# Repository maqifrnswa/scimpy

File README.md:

# Scimpy
Scimpy Speaker Design Tool
Open Source Sound Card Based Speaker Impedance Measurements, Speaker Design Tool, and Book on Loudspeaker Operation

## Requirements
Python 3, Qt4, PortAudio

### General Python Requirements:

scipy, pyaudio, matplotlib, pandas and either pyqt4 or pyside

### Debian/Ubuntu development environment:

```
sudo apt-get install python3-scipy python3-pyaudio python3-matplotlib python3-pyside python3-pandas
```

### Windows Python Environment 
& Scimpy Installation:

#### Full install (LARGE), comes with spyder IDE and many other python packages

install anaconda (https://www.continuum.io/downloads), open anaconda console and then in the anaconda console run "pip install pyaudio".

If you want more control over the sound card, you can use a version of pyaudio built with more APIs available. Download pyaudio from:
http://www.lfd.uci.edu/~gohlke/pythonlibs/ then open the anaconda console and install pyaudio
with "pip install PyAudio-0.2.9-cp35-none-win_amd64.whl"
replacing PyAudio-0.2.9-cp35-none-win_amd64.whl with the name of the file you downloaded.

#### Minimal install:

Install miniconda (32bit, even if you have 64 bit - makes things easier) from:
http://conda.pydata.org/miniconda.html

Open Windows PowerShell (Start Menu, search for "Windows PowerShell") and type the following commands:

```
conda update conda
conda install matplotlib scipy numpy
pip install pyaudio
cd LOCATION_WHERE_SCIMPY_WAS_DOWNLOADED
python run.py
```

have fun!

#### How to build Windows binaries

PyInstaller works. First install pyinstaller:

```
pip install pywin32 pyinstaller
conda install setuptools=19.2
```

(downgrading setuptools: https://github.com/pyinstaller/pyinstaller/issues/1781)

The run

```
pyinstaller -F --additional-hooks-dir=pyinstaller-hooks run.py
```

to get a single executable in dist/

### Book
LaTeX (e.g., MiKTeX)
http://miktex.org/

## License
Code: GPL3

Book/Documentation: CC-BY-SA 4.0

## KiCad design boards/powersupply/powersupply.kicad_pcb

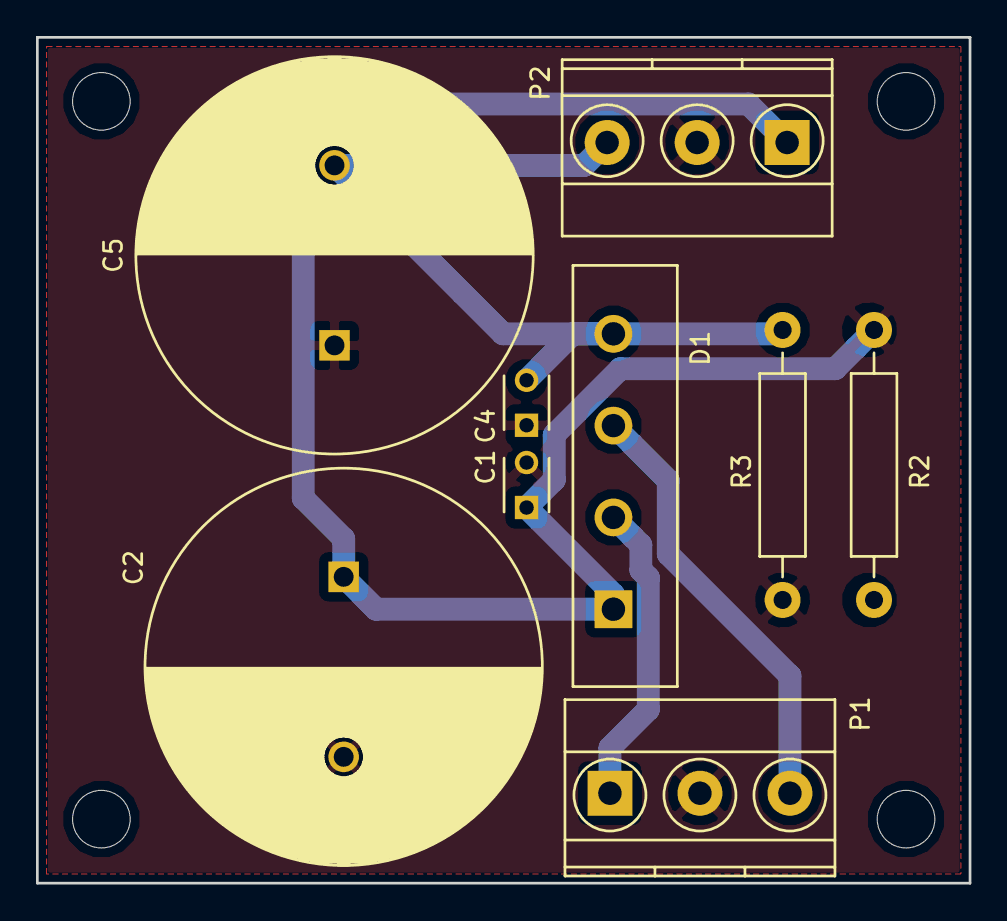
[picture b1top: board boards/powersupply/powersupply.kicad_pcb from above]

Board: 2 copper layers, 51.8 x 47.0 mm, 9 parts (0 on the bottom side), 5 nets.

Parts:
C1, C4: 100n; C_Disc_D3_P2.5
C2, C5: 6800u; C_Radial_D22_L41_P10
D1: Diode_Bridge; Diode_Bridge_18.5x5.5
P1, P2: CONN_01X03; TerminalBlock_Pheonix_MKDS1.5-3pol
R2, R3: 1K 1W; Resistor_Horizontal_RM15mm

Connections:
+15V: C1.1, C2.1, D1.3, P2.1, R2.1
-15V: C4.2, C5.2, D1.1, P2.3, R3.2
/+12VAC: D1.4, P1.3
/-12VAC: D1.2, P1.1
GND: C1.2, C2.2, C4.1, C5.1, P1.2, P2.2, R2.2, R3.1

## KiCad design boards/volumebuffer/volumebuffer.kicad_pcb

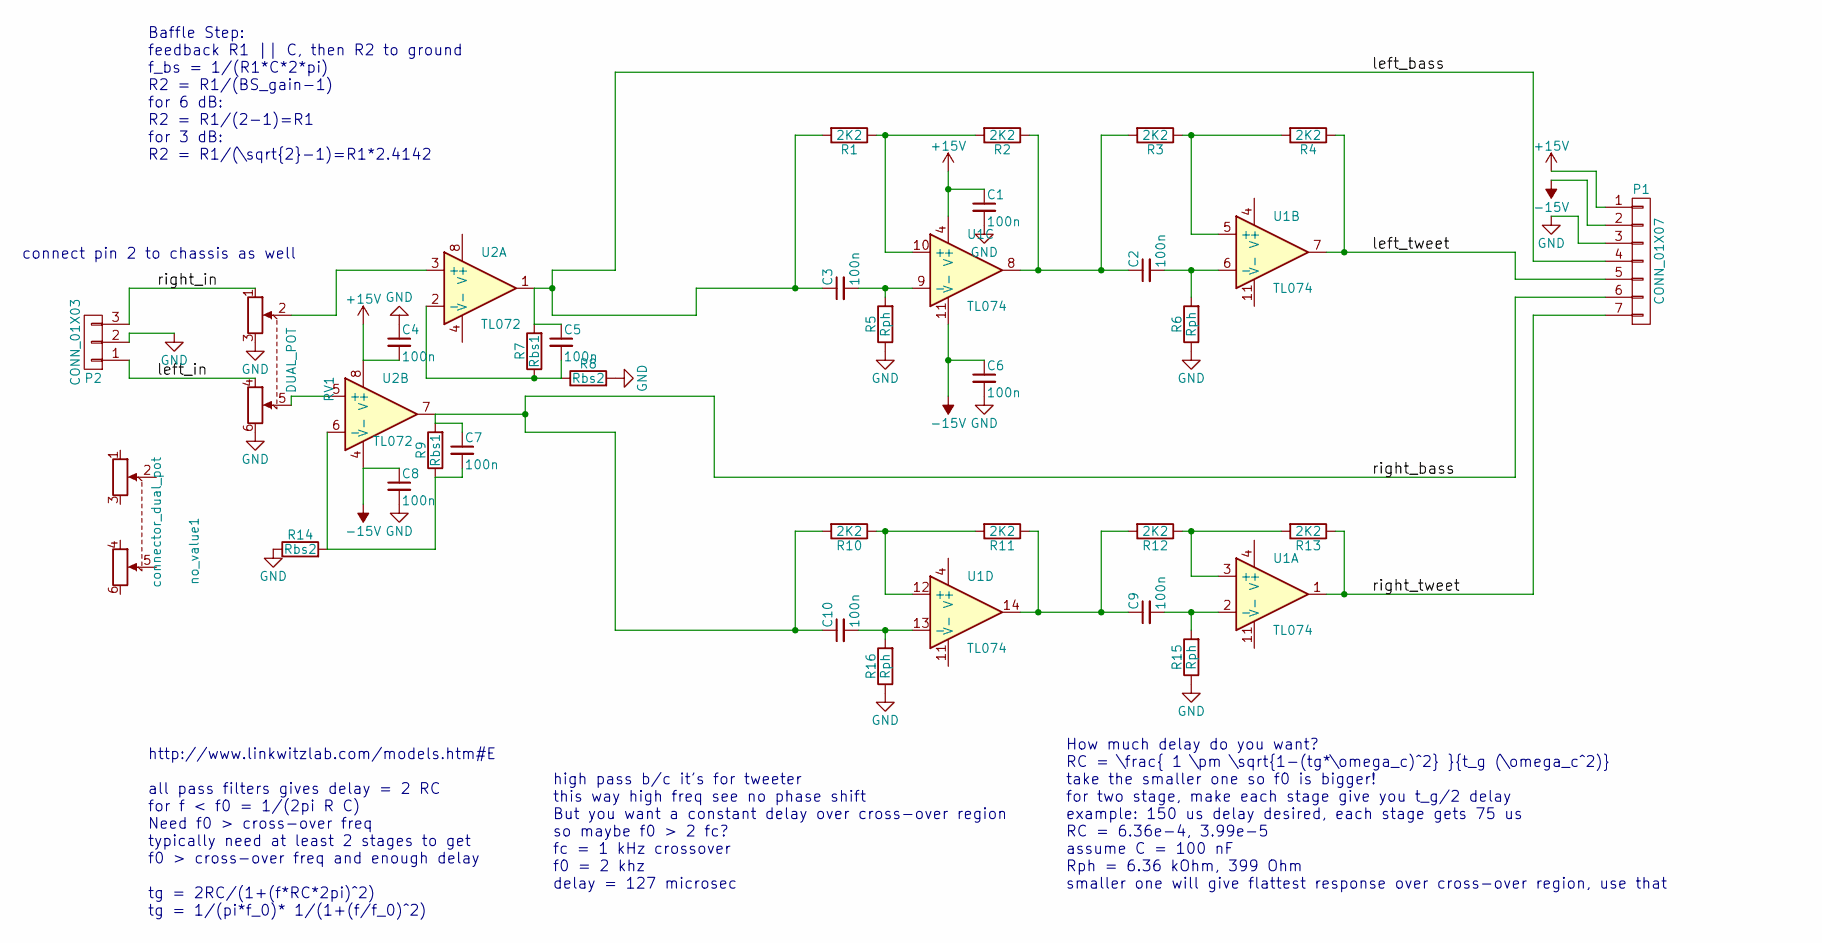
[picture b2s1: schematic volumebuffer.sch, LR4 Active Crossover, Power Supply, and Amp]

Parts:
C1, C4, C6, C8: 100n; C_Disc_D3_P2.5
C2, C3, C5, C7, C9, C10: 100n; C_Disc_D6_P5
P1: CONN_01X07; Socket_Strip_Angled_1x07
P2: CONN_01X03; TerminalBlock_Pheonix_MKDS1.5-3pol
R1, R2, R3, R4, R10, R11, R12, R13: 2K2; R_Axial_DIN0204_L3.6mm_D1.6mm_P5.08mm_Horizontal
R5, R6, R15, R16: Rph; R_Axial_DIN0204_L3.6mm_D1.6mm_P5.08mm_Horizontal
R7, R9: Rbs1; R_Axial_DIN0204_L3.6mm_D1.6mm_P5.08mm_Horizontal
R8, R14: Rbs2; R_Axial_DIN0204_L3.6mm_D1.6mm_P5.08mm_Horizontal
RV1: DUAL_POT; Molex_KK-6410-06_06x2.54mm_Straight
U1: TL074; DIP-14_W7.62mm
U2: TL072; DIP-8_W7.62mm
no_value1: connector_dual_pot

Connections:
+15V: C1.1, C4.2, P1.1, U1.4 (V+), U2.8 (V+)
-15V: C6.1, C8.1, P1.2, U1.11 (V-), U2.4 (V-)
/left_bass: C3.1, C5.1, P1.4, R1.2, R7.2, U2.1
/left_in: P2.1, RV1.4
/left_tweet: P1.5, R4.1, U1.7
/right_bass: C7.1, C10.1, P1.6, R9.2, R10.2, U2.7
/right_in: P2.3, RV1.1
/right_tweet: P1.7, R13.1, U1.1
GND: C1.2, C4.1, C6.2, C8.2, P1.3, P2.2, R5.1, R6.1, R8.2, R14.1, R15.1, R16.1, RV1.3, RV1.6
unnamed: C2.1, R2.1, R3.2, U1.8
unnamed: C2.2, R6.2, U1.6 (-)
unnamed: C3.2, R5.2, U1.9 (-)
unnamed: C5.2, R7.1, R8.1, U2.2 (-)
unnamed: C7.2, R9.1, R14.2, U2.6 (-)
unnamed: C9.1, R11.1, R12.2, U1.14
unnamed: C9.2, R15.2, U1.2 (-)
unnamed: C10.2, R16.2, U1.13 (-)
unnamed: R1.1, R2.2, U1.10 (+)
unnamed: R3.1, R4.2, U1.5 (+)
unnamed: R10.1, R11.2, U1.12 (+)
unnamed: R12.1, R13.2, U1.3 (+)
unnamed: RV1.2, U2.3 (+)
unnamed: RV1.5, U2.5 (+)

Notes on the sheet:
Baffle Step: feedback R1 || C, then R2 to ground f_bs = 1/(R1*C*2*pi) R2 = R1/(BS_gain-1) for 6 dB: R2 = R1/(2-1)=R1 for 3 dB: R2 = R1/(\sqrt{2}-1)=R1*2.4142
connect pin 2 to chassis as well
http://www.linkwitzlab.com/models.htm#E all pass filters gives delay = 2 RC for f < f0 = 1/(2pi R C) Need f0 > cross-over freq typically need at least 2 stages to get f0 > cross-over freq and enough delay tg = 2RC/(1+(f*RC*2pi)^2) tg = 1/(pi*f_0)* 1/(1+(f/f_0)^2)
high pass b/c it's for tweeter this way high freq see no phase shift But you want a constant delay over cross-over region so maybe f0 > 2 fc? fc = 1 kHz crossover f0 = 2 khz delay = 127 microsec
How much delay do you want? RC = \frac{ 1 \pm \sqrt{1-(tg*\omega_c)^2} }{t_g (\omega_c^2)} take the smaller one so f0 is bigger! for two stage, make each stage give you t_g/2 delay example: 150 us delay desired, each stage gets 75 us RC = 6.36e-4, 3.99e-5 assume C = 100 nF Rph = 6.36 kOhm, 399 Ohm 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

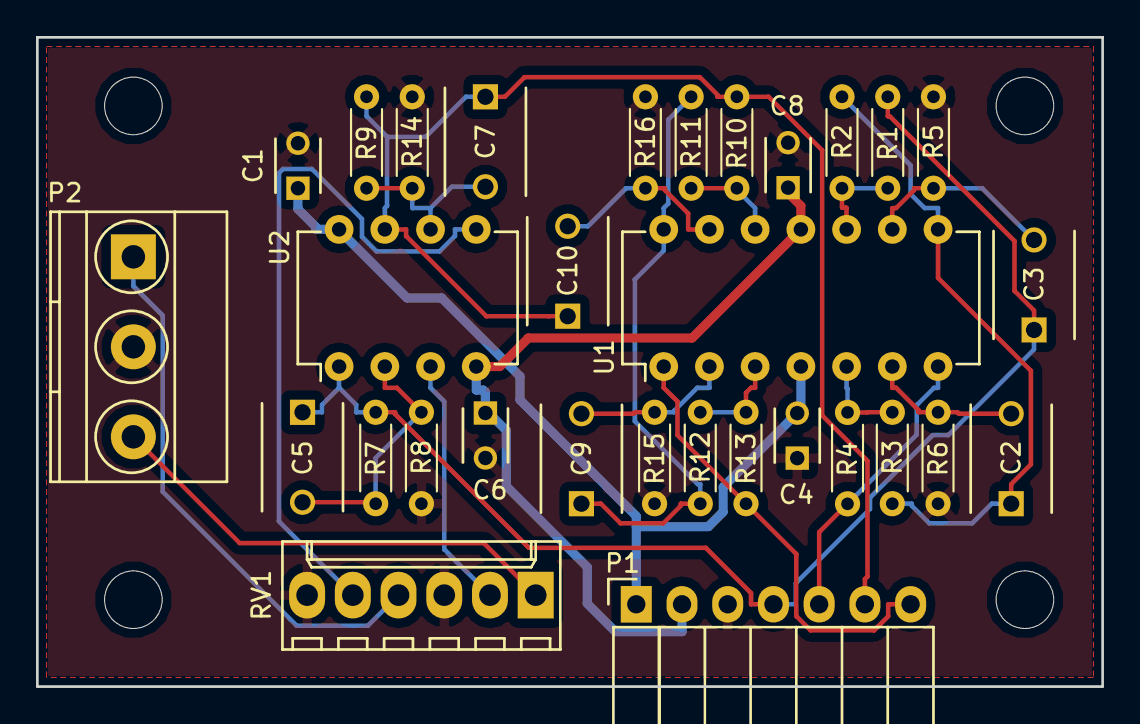
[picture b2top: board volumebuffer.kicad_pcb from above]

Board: 2 copper layers, 59.2 x 36.1 mm, 34 parts (0 on the bottom side), 23 nets.

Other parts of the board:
mnt1, mnt2, mnt3: MountingHole_3.2mm_M3

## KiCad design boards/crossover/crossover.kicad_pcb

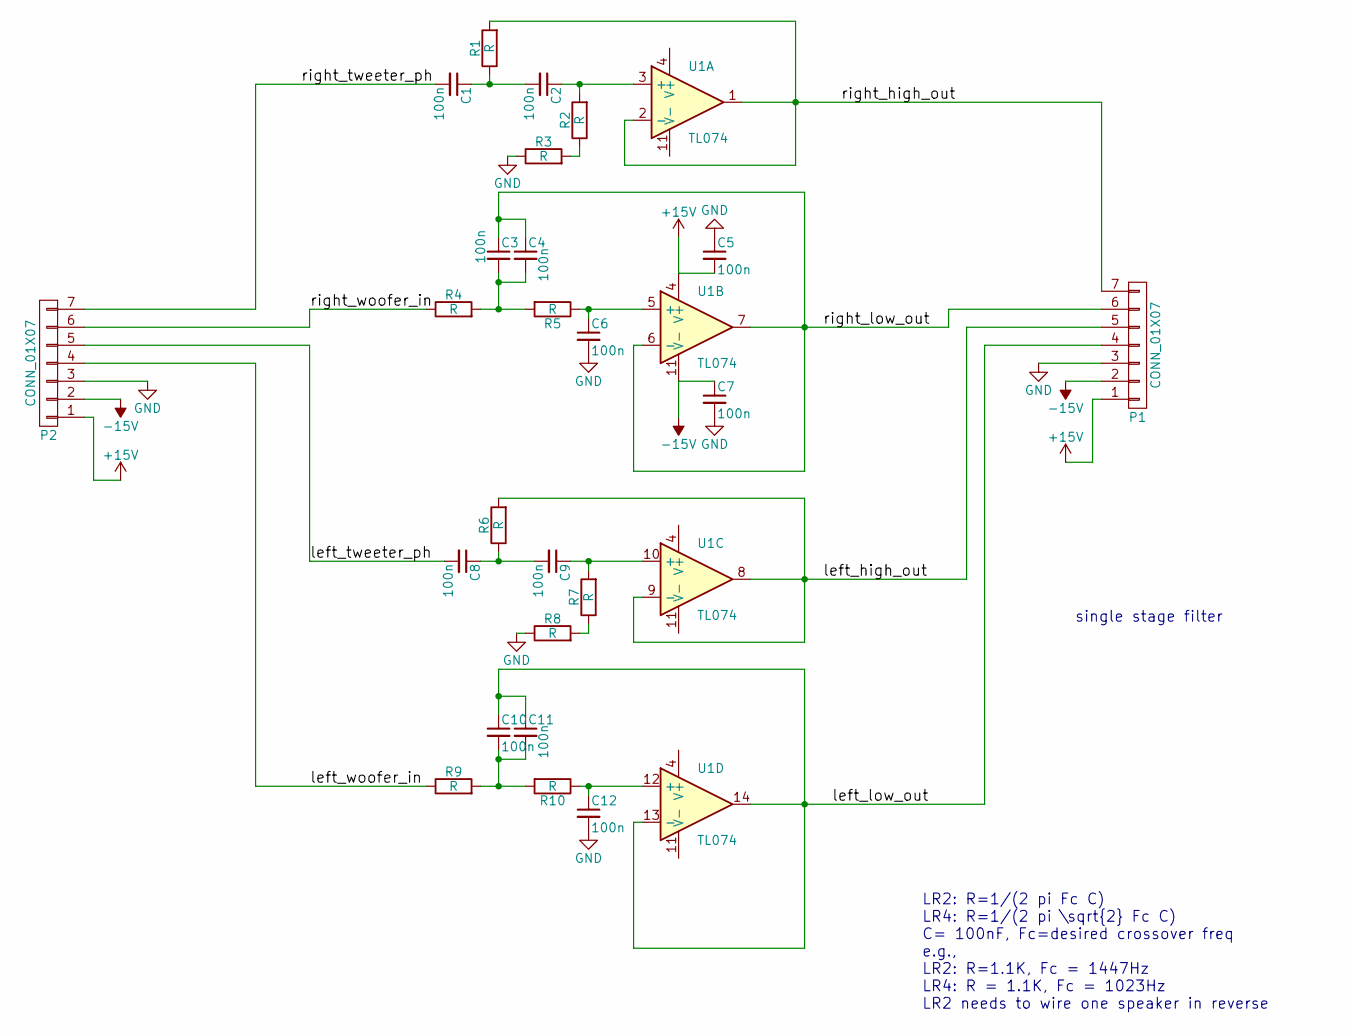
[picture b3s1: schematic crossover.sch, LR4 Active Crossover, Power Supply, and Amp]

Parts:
C1, C2, C3, C4, C6, C8, C9, C10, C11, C12: 100n; C_Disc_D6_P5
C5, C7: 100n; C_Disc_D3_P2.5
P1: CONN_01X07; Socket_Strip_Angled_1x07
P2: CONN_01X07; Pin_Header_Angled_1x07
R1, R2, R3, R4, R5, R6, R7, R8, R9, R10: R; R_Axial_DIN0204_L3.6mm_D1.6mm_P5.08mm_Horizontal
U1: TL074; DIP-14_W7.62mm

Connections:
+15V: C5.2, P1.1, P2.1, U1.4 (V+)
-15V: C7.1, P1.2, P2.2, U1.11 (V-)
/left_high_out: P1.5, R6.2, U1.8, U1.9 (-)
/left_low_out: C10.1, C11.1, P1.4, U1.13 (-), U1.14
/left_tweeter_ph: C8.2, P2.5
/left_woofer_in: P2.4, R9.1
/right_high_out: P1.7, R1.2, U1.1, U1.2 (-)
/right_low_out: C3.1, C4.1, P1.6, U1.6 (-), U1.7
/right_tweeter_ph: C1.2, P2.7
/right_woofer_in: P2.6, R4.1
GND: C5.1, C6.2, C7.2, C12.2, P1.3, P2.3, R3.1, R8.1
unnamed: C1.1, C2.2, R1.1
unnamed: C2.1, R2.2, U1.3 (+)
unnamed: C3.2, C4.2, R4.2, R5.2
unnamed: C6.1, R5.1, U1.5 (+)
unnamed: C8.1, C9.2, R6.1
unnamed: C9.1, R7.2, U1.10 (+)
unnamed: C10.2, C11.2, R9.2, R10.2
unnamed: C12.1, R10.1, U1.12 (+)
unnamed: R2.1, R3.2
unnamed: R7.1, R8.2

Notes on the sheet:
LR2: R=1/(2 pi Fc C) LR4: R=1/(2 pi \sqrt{2} Fc C) C= 100nF, Fc=desired crossover freq e.g., LR2: R=1.1K, Fc = 1447Hz LR4: R = 1.1K, Fc = 1023Hz LR2 needs to wire one speaker in reverse
single stage filter

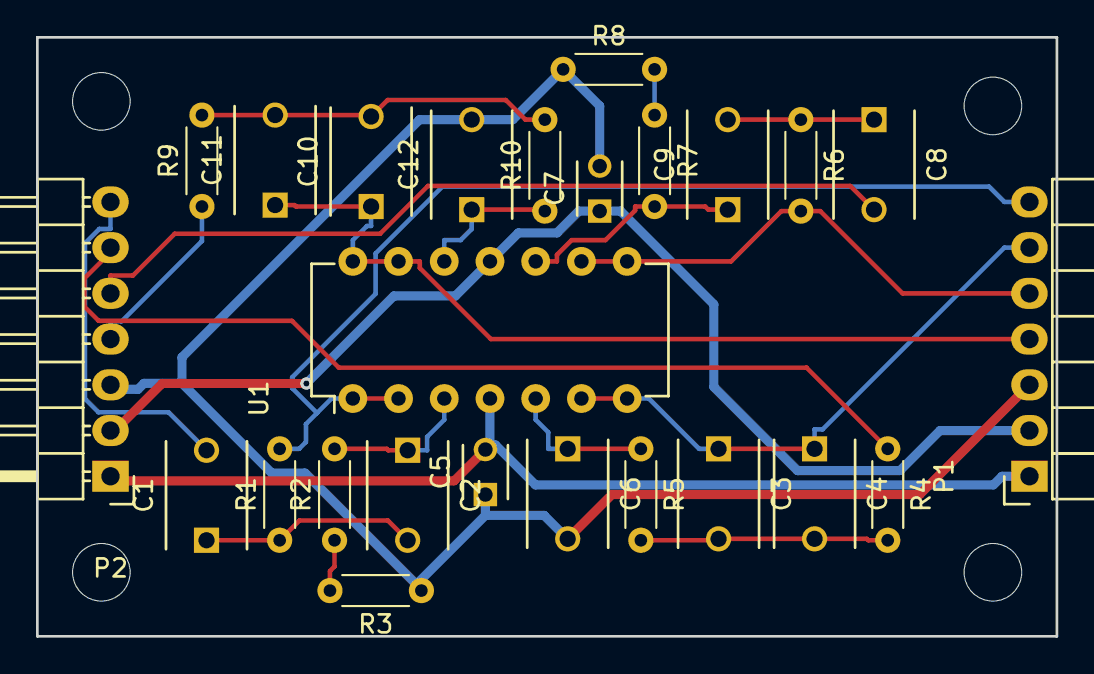
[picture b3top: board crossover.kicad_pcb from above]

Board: 2 copper layers, 56.6 x 33.3 mm, 29 parts (0 on the bottom side), 21 nets.

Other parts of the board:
mnt1, mnt2, mnt3, mnt4: MountingHole_3.2mm_M3

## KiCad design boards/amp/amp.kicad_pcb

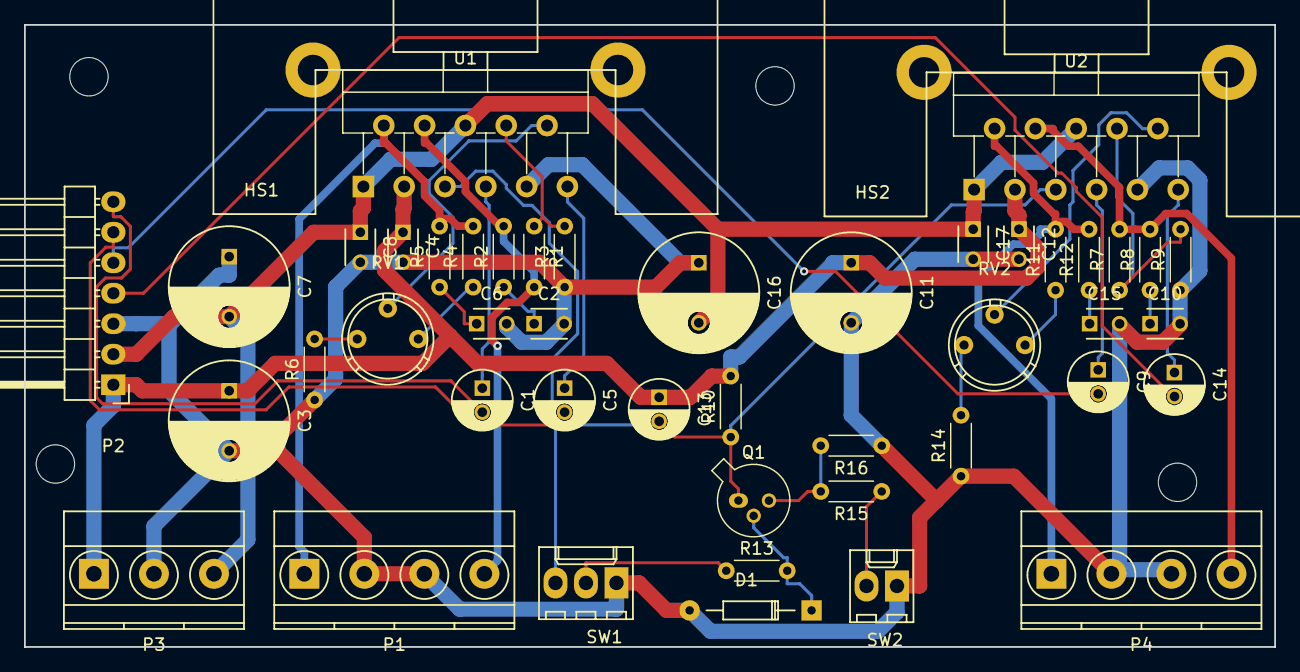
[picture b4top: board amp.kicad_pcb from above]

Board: 2 copper layers, 104.1 x 51.8 mm, 47 parts (0 on the bottom side), 32 nets.

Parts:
C1, C5, C9, C14: 1u-audio; C_Radial_D5_L11_P2
C2, C4, C6, C8, C10, C12, C15, C17: 100n; C_Disc_D3_P2.5
C3, C7, C11, C16: 1000u; C_Radial_D10_L20_P5
C13: 1u; C_Radial_D5_L11_P2
D1: 5.1V; Diode_DO-35_SOD27_Horizontal_RM10
HS1, HS2: multiwatt11_heatsink
P1, P4: CONN_01X04; TerminalBlock_Pheonix_MKDS1.5-4pol
P2: CONN_01X07; Pin_Header_Angled_1x07
P3: CONN_01X03; TerminalBlock_Pheonix_MKDS1.5-3pol
Q1: BC107; TO-18-3
R1, R7: 18K; R_Axial_DIN0204_L3.6mm_D1.6mm_P5.08mm_Horizontal
R2, R5, R8, R12: 4.8R; R_Axial_DIN0204_L3.6mm_D1.6mm_P5.08mm_Horizontal
R3, R9: 560R; R_Axial_DIN0204_L3.6mm_D1.6mm_P5.08mm_Horizontal
R4, R11: 68K; R_Axial_DIN0204_L3.6mm_D1.6mm_P5.08mm_Horizontal
R6, R14: 1K5; R_Axial_DIN0204_L3.6mm_D1.6mm_P5.08mm_Horizontal
R10, R15: 15K; R_Axial_DIN0204_L3.6mm_D1.6mm_P5.08mm_Horizontal
R13: 10K; R_Axial_DIN0204_L3.6mm_D1.6mm_P5.08mm_Horizontal
R16: 47K; R_Axial_DIN0204_L3.6mm_D1.6mm_P5.08mm_Horizontal
RV1, RV2: 1K POT; Potentiometer_Bourns_3339P_Angular_ScrewUp
SW1: Standby; Molex_KK-6410-03_03x2.54mm_Straight
SW2: Mute; Molex_KK-6410-02_02x2.54mm_Straight
U1, U2: TDA7292; Multiwatt-11_Vertical_StaggeredType1

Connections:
+15V: C3.1, C4.1, C11.1, C12.1, C13.1, P2.1, P3.1, R10.2, U1.3, U2.3
-15V: C7.2, C8.1, C16.2, C17.1, P2.2, P3.3, U1.1, U1.6, U2.1, U2.6
/M/SB: C13.2, Q1.1, R10.1, SW1.3, U1.5, U2.5
/left_high_in: C9.2, P2.5
/left_high_out: P4.4, R7.2, R8.2, U2.4
/left_low_in: C14.2, P2.4
/left_low_out: P4.1, R11.2, R12.2, U2.2
/right_high_in: C1.2, P2.7
/right_high_out: P1.4, R1.2, R2.2, U1.4
/right_low_in: C5.2, P2.6
/right_low_out: P1.1, R4.2, R5.2, U1.2
GND: C2.2, C3.2, C4.2, C6.2, C7.1, C8.2, C10.2, C11.2, C12.2, C15.2, C16.1, C17.2, D1.2, P1.2, P1.3, P2.3, P3.2, P4.2, P4.3, R3.1, R6.1, R9.1, R14.1, R16.1, SW1.1, SW2.1, U1.9, U2.9
unnamed: C1.1, U1.7
unnamed: C2.1, R2.1
unnamed: C5.1, U1.11
unnamed: C6.1, R5.1
unnamed: C9.1, U2.7
unnamed: C10.1, R8.1
unnamed: C14.1, U2.11
unnamed: C15.1, R12.1
unnamed: D1.1, Q1.2, R13.2
unnamed: Q1.3, R15.2, R16.2
unnamed: R1.1, R3.2, U1.8
unnamed: R4.1, RV1.3
unnamed: R6.2, RV1.1
unnamed: R7.1, R9.2, U2.8
unnamed: R11.1, RV2.3
unnamed: R13.1, SW1.2
unnamed: R14.2, RV2.1
unnamed: R15.1, SW2.2
unnamed: RV1.2, U1.10
unnamed: RV2.2, U2.10

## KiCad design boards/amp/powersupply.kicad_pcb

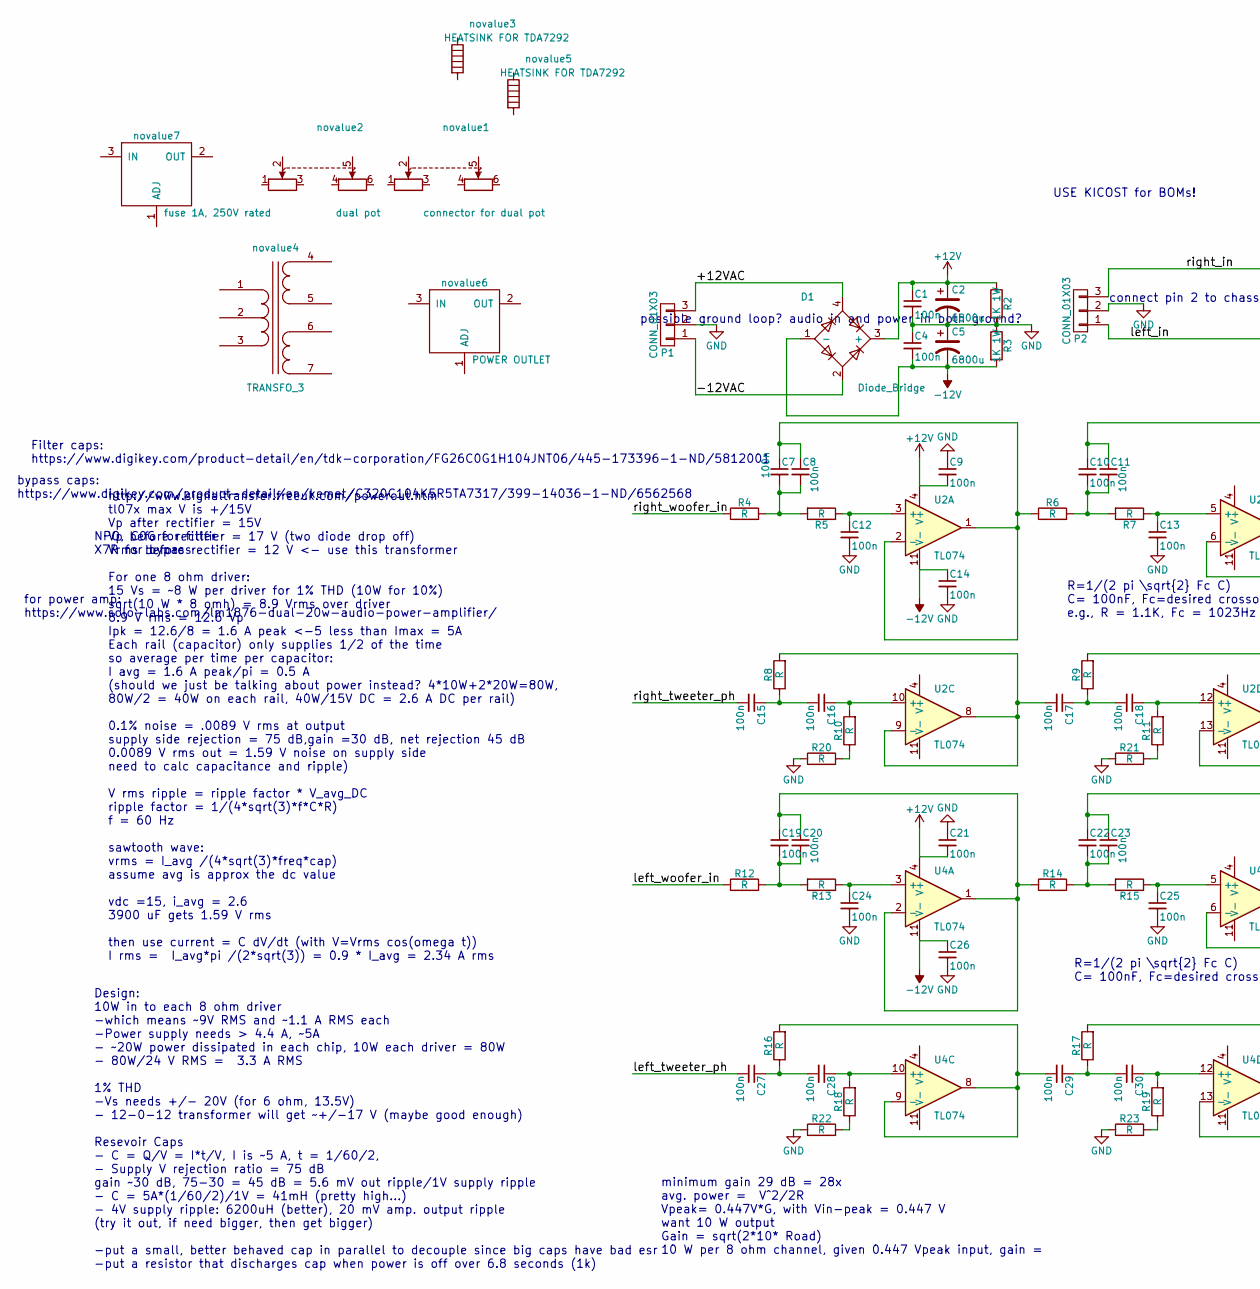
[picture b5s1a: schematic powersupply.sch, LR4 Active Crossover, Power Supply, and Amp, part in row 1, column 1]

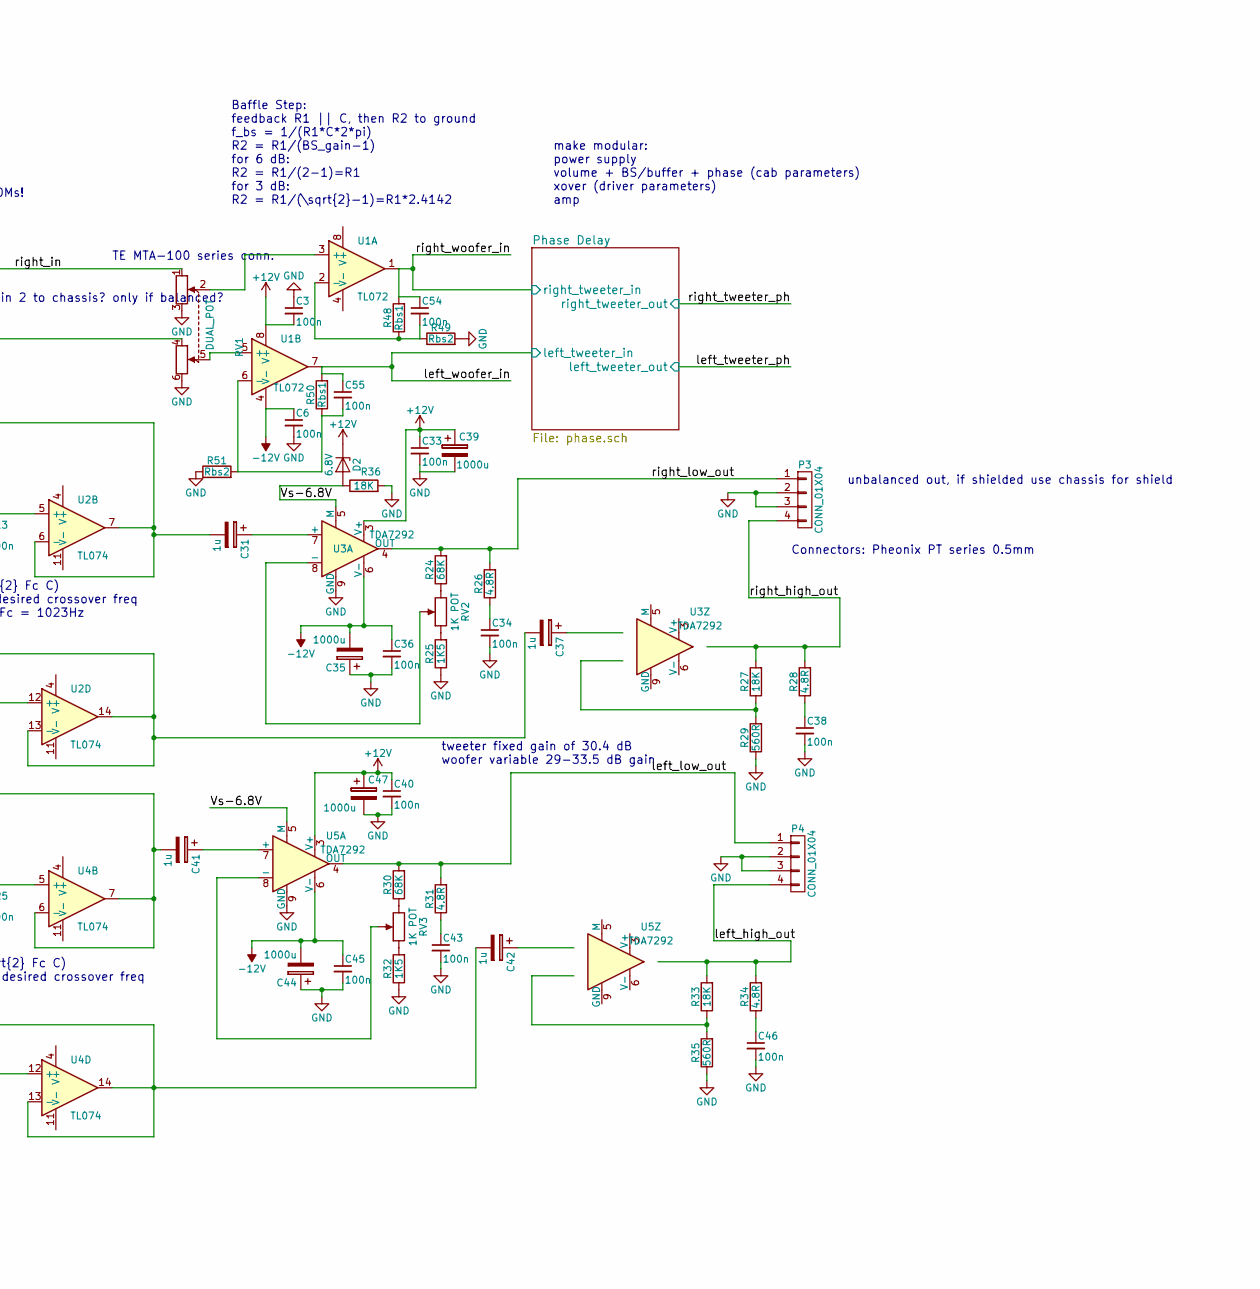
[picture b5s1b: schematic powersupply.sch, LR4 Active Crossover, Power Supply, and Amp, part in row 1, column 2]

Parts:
C1, C3, C4, C6, C9, C14, C21, C26, C33, C34, C36, C38, C40, C43, C45, C46: 100n; C_Disc_D3_P2.5
C2, C5: 6800u; C_Radial_D22_L41_P10
C7, C8, C10, C11, C12, C13, C15, C16, C17, C18, C19, C20, C22, C23, C24, C25, C27, C28, C29, C30, C54, C55: 100n; C_Disc_D6_P5
C31, C37, C41, C42: 1u; C_Radial_D5_L11_P2
C35, C39, C44, C47: 1000u; C_Radial_D10_L20_P5
D1: Diode_Bridge; Diode_Bridge_18.5x5.5
D2: 6.8V; Diode_DO-35_SOD27_Horizontal_RM10
P1, P2: CONN_01X03; TerminalBlock_Pheonix_MKDS1.5-3pol
P3, P4: CONN_01X04; TerminalBlock_Pheonix_MKDS1.5-4pol; digikey# 277-1579-ND
R2, R3: 1K 1W; Resistor_Horizontal_RM15mm
R4, R5, R6, R7, R8, R9, R10, R11, R12, R13, R14, R15, R16, R17, R18, R19, R20, R21, R22, R23: R; R_Axial_DIN0204_L3.6mm_D1.6mm_P5.08mm_Horizontal
R24, R30: 68K; R_Axial_DIN0204_L3.6mm_D1.6mm_P5.08mm_Horizontal
R25, R32: 1K5; R_Axial_DIN0204_L3.6mm_D1.6mm_P5.08mm_Horizontal
R26, R28, R31, R34: 4.8R; R_Axial_DIN0204_L3.6mm_D1.6mm_P5.08mm_Horizontal
R27, R33, R36: 18K; R_Axial_DIN0204_L3.6mm_D1.6mm_P5.08mm_Horizontal
R29, R35: 560R; R_Axial_DIN0204_L3.6mm_D1.6mm_P5.08mm_Horizontal
R48, R50: Rbs1; R_Axial_DIN0204_L3.6mm_D1.6mm_P5.08mm_Horizontal
R49, R51: Rbs2; R_Axial_DIN0204_L3.6mm_D1.6mm_P5.08mm_Horizontal
RV1: DUAL_POT; Molex_KK-6410-06_06x2.54mm_Straight
RV2, RV3: 1K POT; Potentiometer_Bourns_3339P_Angular_ScrewUp
U1: TL072; DIP-8_W7.62mm
U2, U4: TL074; DIP-14_W7.62mm
U3, U5: TDA7292; Multiwatt-11_Vertical_StaggeredType1
novalue1: connector for dual pot
novalue2: dual pot
novalue3, novalue5: HEATSINK FOR TDA7292
novalue4: TRANSFO_3
novalue6: POWER OUTLET
novalue7: fuse 1A, 250V rated

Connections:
+12V: C1.1, C2.1, C3.2, C9.2, C21.2, C33.1, C39.1, C40.1, C47.1, D1.3 (+), D2.1 (K), R2.1, U1.8 (V+), U2.4 (V+), U3.3 (V+), U4.4 (V+), U5.3 (V+); also elsewhere on the board
/+12VAC: D1.4, P1.3
/-12VAC: D1.2, P1.1
/Vs-6.8V: D2.2 (A), R36.1, U3.5 (M), U5.5 (M)
/left_high_out: P4.4, R33.2, R34.2
/left_in: P2.1, RV1.4
/left_low_out: P4.1, R30.2, R31.2, U5.4 (OUT)
/left_tweeter_ph: C27.2; also elsewhere on the board
/left_woofer_in: C55.1, R12.1, R50.2, U1.7; also elsewhere on the board
/right_high_out: P3.4, R27.2, R28.2
/right_in: P2.3, RV1.1
/right_low_out: P3.1, R24.2, R26.2, U3.4 (OUT)
/right_tweeter_ph: C15.2; also elsewhere on the board
/right_woofer_in: C54.1, R4.1, R48.2, U1.1; also elsewhere on the board
GND: C1.2, C2.2, C3.1, C4.1, C5.1, C6.2, C9.1, C12.2, C13.2, C14.2, C21.1, C24.2, C25.2, C26.2, C33.2, C34.2, C35.1, C36.2, C38.2, C39.2, C40.2, C43.2, C44.1, C45.2, C46.2, C47.2, P1.2, P2.2, P3.2, P3.3, P4.2, P4.3, R2.2, R3.1, R20.1, R21.1, R22.1, R23.1, R25.1, R29.1, R32.1, R35.1, R36.2, R49.2, R51.1, RV1.3, RV1.6, U3.9 (GND), U5.9 (GND); also elsewhere on the board
unnamed: C7.1, C8.1, R6.1, U2.1, U2.2 (-)
unnamed: C7.2, C8.2, R4.2, R5.2
unnamed: C10.1, C11.1, C31.2, U2.6 (-), U2.7
unnamed: C10.2, C11.2, R6.2, R7.2
unnamed: C12.1, R5.1, U2.3 (+)
unnamed: C13.1, R7.1, U2.5 (+)
unnamed: C15.1, C16.2, R8.1
unnamed: C16.1, R10.2, U2.10 (+)
unnamed: C17.1, C18.2, R9.1
unnamed: C17.2, R8.2, U2.8, U2.9 (-)
unnamed: C18.1, R11.2, U2.12 (+)
unnamed: C19.1, C20.1, R14.1, U4.1, U4.2 (-)
unnamed: C19.2, C20.2, R12.2, R13.2
unnamed: C22.1, C23.1, C41.2, U4.6 (-), U4.7
unnamed: C22.2, C23.2, R14.2, R15.2
unnamed: C24.1, R13.1, U4.3 (+)
unnamed: C25.1, R15.1, U4.5 (+)
unnamed: C27.1, C28.2, R16.1
unnamed: C28.1, R18.2, U4.10 (+)
unnamed: C29.1, C30.2, R17.1
unnamed: C29.2, R16.2, U4.8, U4.9 (-)
unnamed: C30.1, R19.2, U4.12 (+)
unnamed: C31.1, U3.7 (+)
unnamed: C34.1, R26.1
unnamed: C37.2, R9.2, U2.13 (-), U2.14
unnamed: C38.1, R28.1
unnamed: C41.1, U5.7 (+)
unnamed: C42.2, R17.2, U4.13 (-), U4.14
unnamed: C43.1, R31.1
unnamed: C46.1, R34.1
unnamed: C54.2, R48.1, R49.1, U1.2 (-)
unnamed: C55.2, R50.1, R51.2, U1.6 (-)
unnamed: R10.1, R20.2
unnamed: R11.1, R21.2
unnamed: R18.1, R22.2
unnamed: R19.1, R23.2
unnamed: R24.1, RV2.3
unnamed: R25.2, RV2.1
unnamed: R27.1, R29.2
unnamed: R30.1, RV3.3
unnamed: R32.2, RV3.1
unnamed: R33.1, R35.2
unnamed: RV1.2, U1.3 (+)
unnamed: RV1.5, U1.5 (+)
unnamed: RV2.2, U3.8 (-)
unnamed: RV3.2, U5.8 (-)

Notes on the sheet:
R=1/(2 pi \sqrt{2} Fc C) C= 100nF, Fc=desired crossover freq e.g., R = 1.1K, Fc = 1023Hz
R=1/(2 pi \sqrt{2} Fc C) C= 100nF, Fc=desired crossover freq
for power amp: https://www.solo-labs.com/lm1876-dual-20w-audio-power-amplifier/
NPO, C0G for filter X7R for bypass
Filter caps: https://www.digikey.com/product-detail/en/tdk-corporation/FG26C0G1H104JNT06/445-173396-1-ND/5812001
bypass caps: https://www.digikey.com/product-detail/en/kemet/C320C104K5R5TA7317/399-14036-1-ND/6562568
Design: 10W in to each 8 ohm driver -which means ~~9V RMS and ~~1.1 A RMS each -Power supply needs > 4.4 A, ~~5A - ~~20W power dissipated in each chip, 10W each driver = 80W - 80W/24 V RMS = 3.3 A RMS 1% THD -Vs needs +/- 20V (for 6 ohm, 13.5V) - 12-0-12 transformer will get ~~+/-17 V (maybe good e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
minimum gain 29 dB = 28x avg. power = V^2/2R Vpeak= 0.447V*G, with Vin-peak = 0.447 V want 10 W output Gain = sqrt(2*10* Road) 10 W per 8 ohm channel, given 0.447 Vpeak input, gain =
Baffle Step: feedback R1 || C, then R2 to ground f_bs = 1/(R1*C*2*pi) R2 = R1/(BS_gain-1) for 6 dB: R2 = R1/(2-1)=R1 for 3 dB: R2 = R1/(\sqrt{2}-1)=R1*2.4142
Connectors: Pheonix PT series 0.5mm
tweeter fixed gain of 30.4 dB woofer variable 29-33.5 dB gain
TE MTA-100 series conn.
connect pin 2 to chassis? only if balanced?
unbalanced out, if shielded use chassis for shield
USE KICOST for BOMs!
http://www.signaltransfer.freeuk.com/powerout.htm tl07x max V is +/15V Vp after rectifier = 15V Vp before rectifier = 17 V (two diode drop off) Vrms before rectifier = 12 V <- use this transformer For one 8 ohm driver: 15 Vs = ~~8 W per driver for 1% THD (10W for 10%) sqrt(10 W * 8 omh) = 8.9 Vrms 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
possible ground loop? audio in and power in both ground?
make modular: power supply volume + BS/buffer + phase (cab parameters) xover (driver parameters) amp

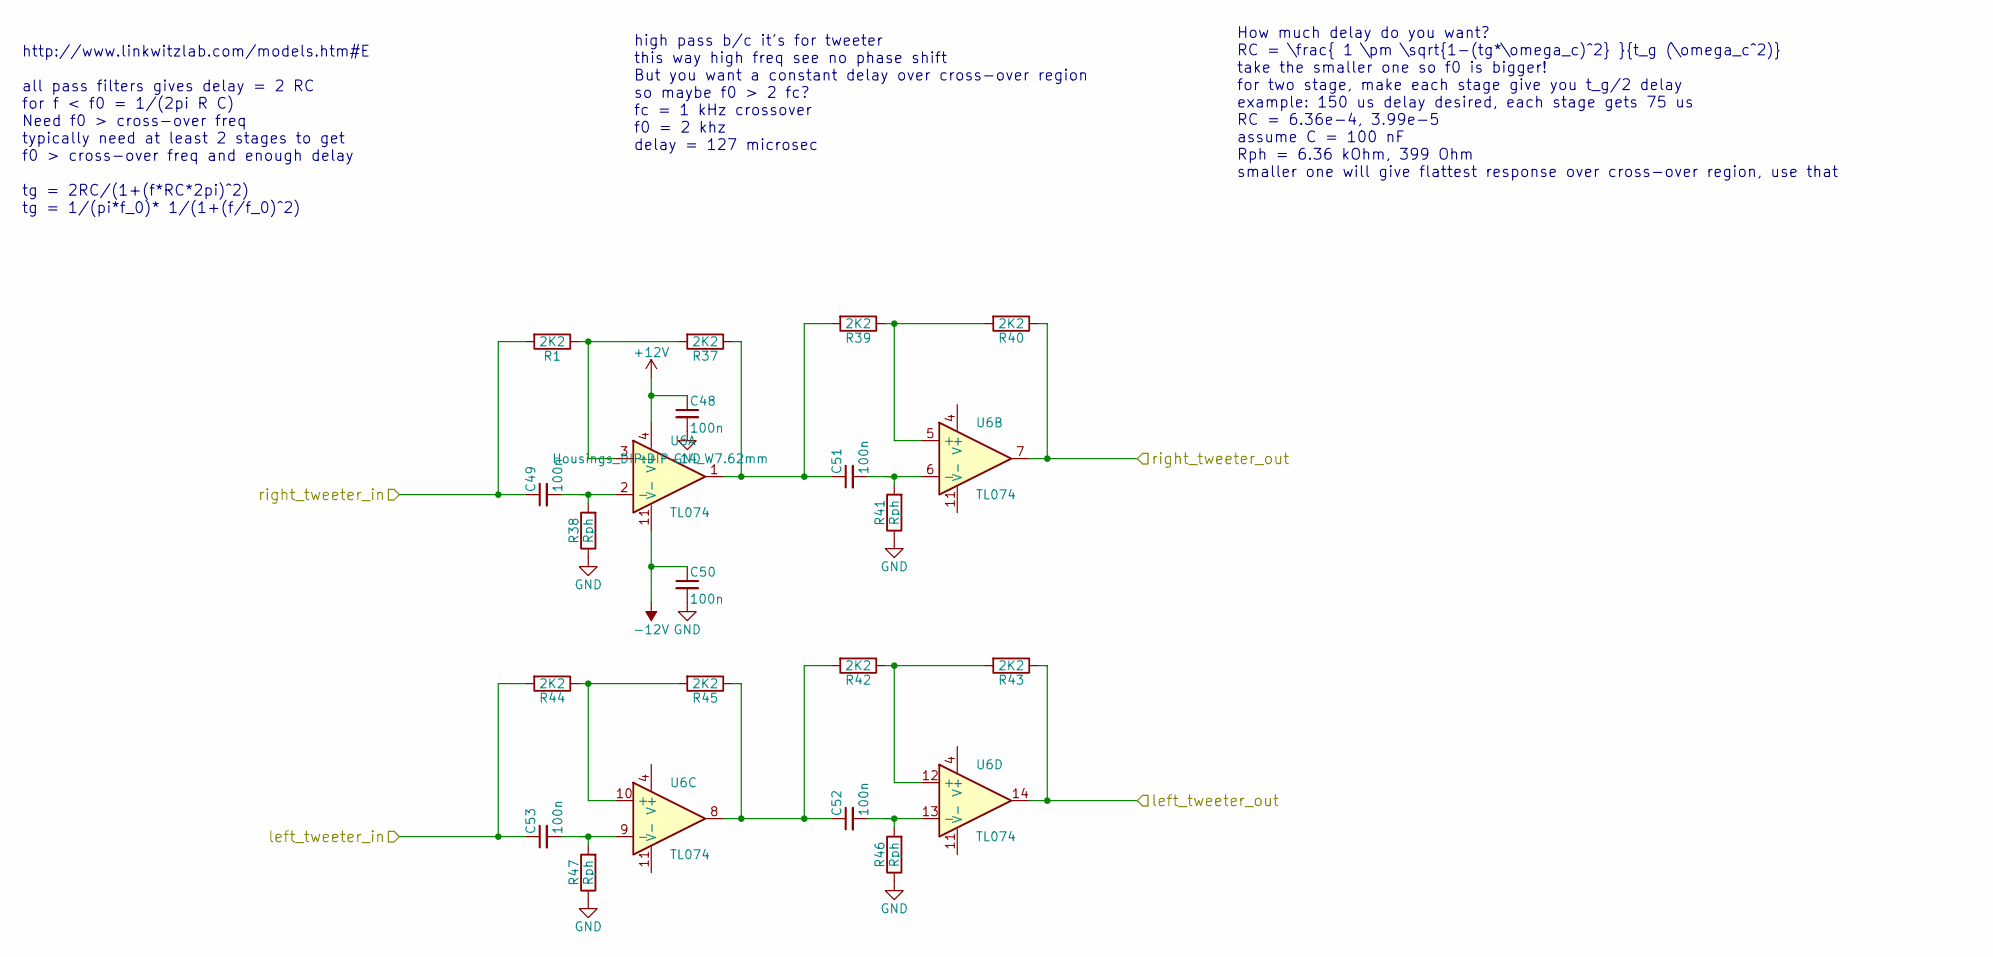
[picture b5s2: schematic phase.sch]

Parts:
C48, C50: 100n; C_Disc_D3_P2.5
C49, C51, C52, C53: 100n; C_Disc_D6_P5
R1, R37, R39, R40, R42, R43, R44, R45: 2K2; Resistor_Horizontal_RM7mm
R38, R41, R46, R47: Rph; Resistor_Horizontal_RM7mm
U6: TL074; DIP-14_W7.62mm

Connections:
+12V: C48.1, U6.4 (V+); also elsewhere on the board
/left_tweeter_ph: R43.1, U6.14; also elsewhere on the board
/left_woofer_in: C53.1, R44.2; also elsewhere on the board
/right_tweeter_ph: R40.1, U6.7; also elsewhere on the board
/right_woofer_in: C49.1, R1.2; also elsewhere on the board
GND: C48.2, C50.2, R38.1, R41.1, R46.1, R47.1; also elsewhere on the board
unnamed: C49.2, R38.2, U6.2 (-)
unnamed: C51.1, R37.1, R39.2, U6.1
unnamed: C51.2, R41.2, U6.6 (-)
unnamed: C52.1, R42.2, R45.1, U6.8
unnamed: C52.2, R46.2, U6.13 (-)
unnamed: C53.2, R47.2, U6.9 (-)
unnamed: R1.1, R37.2, U6.3 (+)
unnamed: R39.1, R40.2, U6.5 (+)
unnamed: R42.1, R43.2, U6.12 (+)
unnamed: R44.1, R45.2, U6.10 (+)

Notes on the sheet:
http://www.linkwitzlab.com/models.htm#E all pass filters gives delay = 2 RC for f < f0 = 1/(2pi R C) Need f0 > cross-over freq typically need at least 2 stages to get f0 > cross-over freq and enough delay tg = 2RC/(1+(f*RC*2pi)^2) tg = 1/(pi*f_0)* 1/(1+(f/f_0)^2)
high pass b/c it's for tweeter this way high freq see no phase shift But you want a constant delay over cross-over region so maybe f0 > 2 fc? fc = 1 kHz crossover f0 = 2 khz delay = 127 microsec
How much delay do you want? RC = \frac{ 1 \pm \sqrt{1-(tg*\omega_c)^2} }{t_g (\omega_c^2)} take the smaller one so f0 is bigger! for two stage, make each stage give you t_g/2 delay example: 150 us delay desired, each stage gets 75 us RC = 6.36e-4, 3.99e-5 assume C = 100 nF Rph = 6.36 kOhm, 399 Ohm 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

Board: 2 copper layers, 120 parts (0 on the bottom side), 72 nets, no tracks yet.

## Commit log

2016-02-13 some more work
2016-02-14 add back docs
2016-02-15 updated doc
2016-02-17 some more docs, and sine sweep
2016-02-19 added matlab plots
2016-02-24 documentation
2016-02-25 more doc
2016-02-28 more docs
2016-03-01 added speakermodel code, more docs, added code to calculate speaker parameters
2016-03-03 documentation and cleaner TS modeler
2016-03-04 some code clean up, added scimpy.spec for pyinstaller building
2016-03-04 added Makefile
2016-03-04 set up modules and setuptools script
2016-03-06 lots more changes
2016-03-06 add screenshot
2016-03-06 added windows screenshot
2016-03-07 fix some docs, update vented box UI code
2016-03-07 working C4 sealed box
2016-03-07 Allow non-default sound card to be used. Allow choosing separate input and output sound cards.
2016-03-07 display suggested input buffer size; put figures in own threads
2016-03-07 don't call widget show() in init
2016-03-08 PEP8 cleaning; docstrings added
2016-03-08 Don't call calculations ideal closes #8
2016-03-08 fix typo, thanks pylint!
2016-03-08 ported box QB3-B4-C4 alignment finished!
2016-03-08 start of unified application
2016-03-08 avoid naming conflicts, use more standard python layout and setup.py
2016-03-08 put plots back on the same blocking thread for now
2016-03-08 made UI more object oriented, implimented docked tabs for tools
2016-03-09 update setup.py scripts
2016-03-09 use central widget for plotting of data
2016-03-09 use the same qt backend that matplotlib uses
2016-03-09 use two plots in central figure
2016-03-10 fixed speaker modeler btn was connected to wrong callback
2016-03-10 put xlabel back
2016-03-10 smart ticks
2016-03-11 use matplotlib.ticker.LinearLocator instead of custom code
2016-03-12 pyinstaller now works on windows
2016-03-12 allow testing of two different in/out devices
2016-03-13 save driver parameters
2016-03-13 added tool tips
2016-03-15 added ZRA file writing
2016-03-20 added fitting routines
2016-03-21 update pyinstaller stuff
2016-03-22 fixed importing ZMA files
2016-03-23 add plot hold control closes #12
2016-03-29 impfitter: use field keys as initial values and export data to speaker modeler
2016-04-01 first work on progress bar for fitting and measurement routines
2016-04-01 make program python2 compatible
2017-03-20 small edits in doc
2017-03-20 fix qt4 import (need to import first)
2017-03-20 significantly increased fit stabillity - it rocks now!
2017-03-21 add eddy current resistance, will need to do two fits - one to 1 kHz to find TS parameters, then to 20 kHz if you want reddy
2017-03-21 use Leach's voice coil impedance, set bounds in fitter. Need to code bounds better (0 to 10x init guess?)
2017-03-21 added bounds to speaker fitting, next step: speaker model with Zl=K(j omega)^n, which is Le=K with n=1 for standard Le
2017-03-22 model completely uses frequency dependent voice coil inductance and eddy current resistance
2017-03-22 updated text in document on frequency dependent impedances
2017-03-22 fixed bug w/ fields not updating after loading drivers
2017-03-23 Fix typo in radiated power documentation, fixes #20
2017-03-23 fix python 2 compat, update setup.py for next release
2017-03-24 update readme and setup scripts
2017-03-24 new release
2017-03-24 update to pyqt5 fixes #22
2017-03-26 fixes for PyQt5
2017-03-28 fix bug on windows/anaconda impedance test failure
2017-03-28 streamline signal generation
2017-03-28 added some debian packaging
2017-04-05 added crossover boards
2017-04-06 upadated boards
2017-04-06 updated debian packaging
2017-04-06 updated debian dependencies
2017-04-06 add section:science to debian packaging'
2017-04-07 add desktop file and icon
2017-04-07 added screenshot for diyaudio post
2017-04-07 some board work, added windows appveyor file
2017-04-07 fix appveyor.yml
2017-04-07 more appveyor fixes
2017-04-07 more fixes
2017-04-07 downgrade appveyor to python2.4
2017-04-07 added upx and tbb.dll to appveyor
2017-04-07 use tbb.lib, rename artifact
2017-04-07 add timestamp to build artifact
2017-04-07 use buildnumber instead of timestamp
2017-04-07 use tbb.dll instead of .lib
2017-04-07 upx screws up qt dlls
    see pyinstaller/1688
2017-04-07 try to use upx with qt5-plugins
    work around for see pyinstaller/#1688
2017-04-07 fix move command on windows
2017-04-07 fix spelling error
2017-04-07 still trying to coax appveyor to build...
2017-04-07 use upx once again
2017-04-07 package first, then upload artifact
2017-04-08 lots of updates, only trigger appveyor builds explicitly in commit message
2017-04-08 only build if the word build is in [] in a commit message
2017-04-15 first working impedance measurements
2017-04-17 warn user of buffer under/over runs fixes #25, and some formatting fixes
2017-04-17 added usage documentation, time for a windows [build]
2017-04-18 fixes to make impedance measuring easier
2017-04-18 allow user to choose fit range (useful for badly behaving speakers)
2017-04-19 documentation html added
2017-04-19 point to new documentation location
2017-04-19 cleaning up documentation files
2017-04-19 L/A works, changed units, fixes #17
2017-04-19 added logging, closes #24
2017-04-19 some pylint fixes
2017-04-19 added some docstrings
2017-04-20 updated docs
2017-04-24 documentation, pcb updates, some pylint fixes
2017-04-27 some board updates
2017-05-04 updated board
2017-05-07 updated boards
2017-05-09 board updates
2017-06-02 more boards work
2017-06-04 Check if axes.autolimit_mode is supported in matplotlib, closes #28
